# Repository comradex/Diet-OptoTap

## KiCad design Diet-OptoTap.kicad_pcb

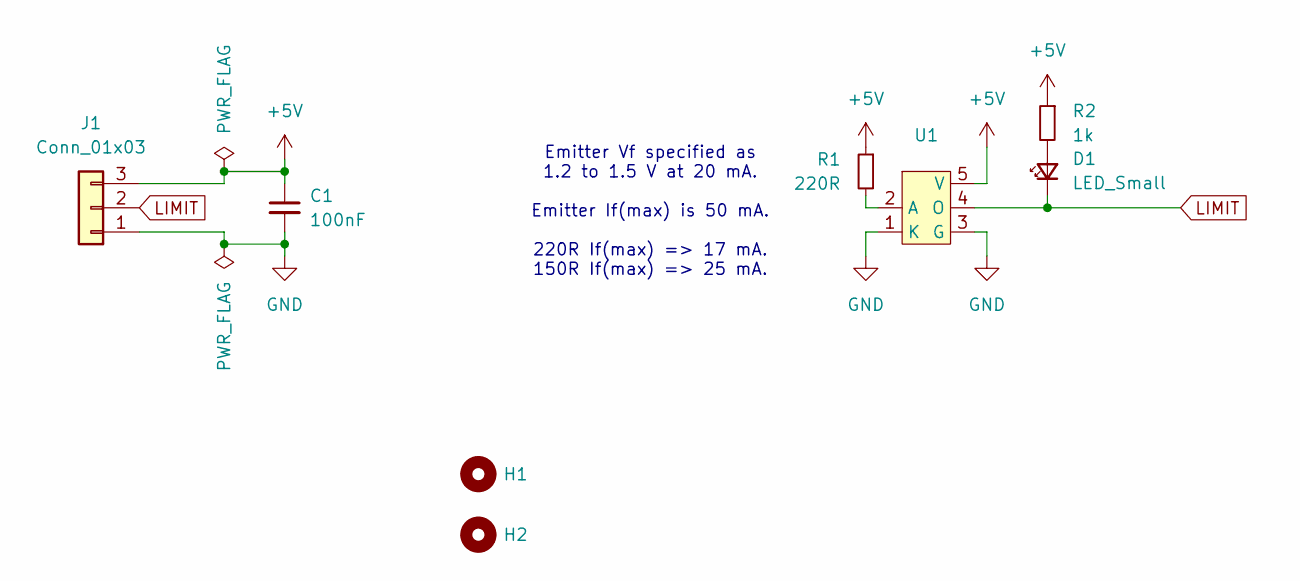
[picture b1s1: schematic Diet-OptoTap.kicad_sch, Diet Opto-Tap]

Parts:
C1: 100nF; C_0603_1608Metric_Pad1.08x0.95mm_HandSolder
D1: LED_Small; LED_0603_1608Metric_Pad1.05x0.95mm_HandSolder
H1, H2: MountingHole; MountingHole_3.2mm_M3
J1: Conn_01x03; PinHeader_1x03_P2.54mm_Vertical
R1: 220R; R_0603_1608Metric_Pad0.98x0.95mm_HandSolder
R2: 1k; R_0603_1608Metric_Pad0.98x0.95mm_HandSolder
U1: EE-SX398

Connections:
+5V: C1.1, J1.3, R1.1, R2.1, U1.5 (V)
GND: C1.2, J1.1, U1.1 (K), U1.3 (G)
LIMIT: D1.1 (K), J1.2, U1.4 (O)
unnamed: D1.2 (A), R2.2
unnamed: R1.2, U1.2 (A)

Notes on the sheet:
Emitter Vf specified as 1.2 to 1.5 V at 20 mA. Emitter If(max) is 50 mA. 220R If(max) => 17 mA. 150R If(max) => 25 mA.

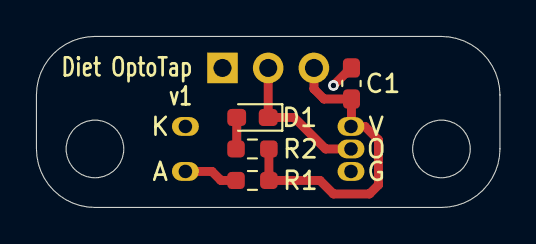
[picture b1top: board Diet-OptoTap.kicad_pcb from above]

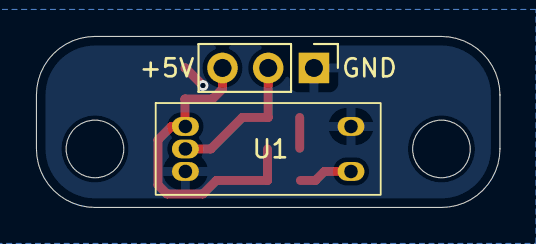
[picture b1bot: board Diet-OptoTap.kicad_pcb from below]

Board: 2 copper layers, 25.8 x 9.5 mm, 8 parts (2 on the bottom side), 5 nets.

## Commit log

2025-02-16 As manufactured for v1.
